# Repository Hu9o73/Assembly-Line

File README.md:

# Assembly Line

Projet Assembly Line : L'objectif étant de créer une machine fabricant des drones à la chaine.

Note: Par manque de fonds, le projet a été arrêté à la fin de la phase de conception. Le document UROP-PrésentationProjetComplet.pdf recense nos travaux.

Projet réalisé en collaboartion avec Théo Lissarague. Son profil GitHub peut être retrouvé dans la liste des contributeurs au projet.

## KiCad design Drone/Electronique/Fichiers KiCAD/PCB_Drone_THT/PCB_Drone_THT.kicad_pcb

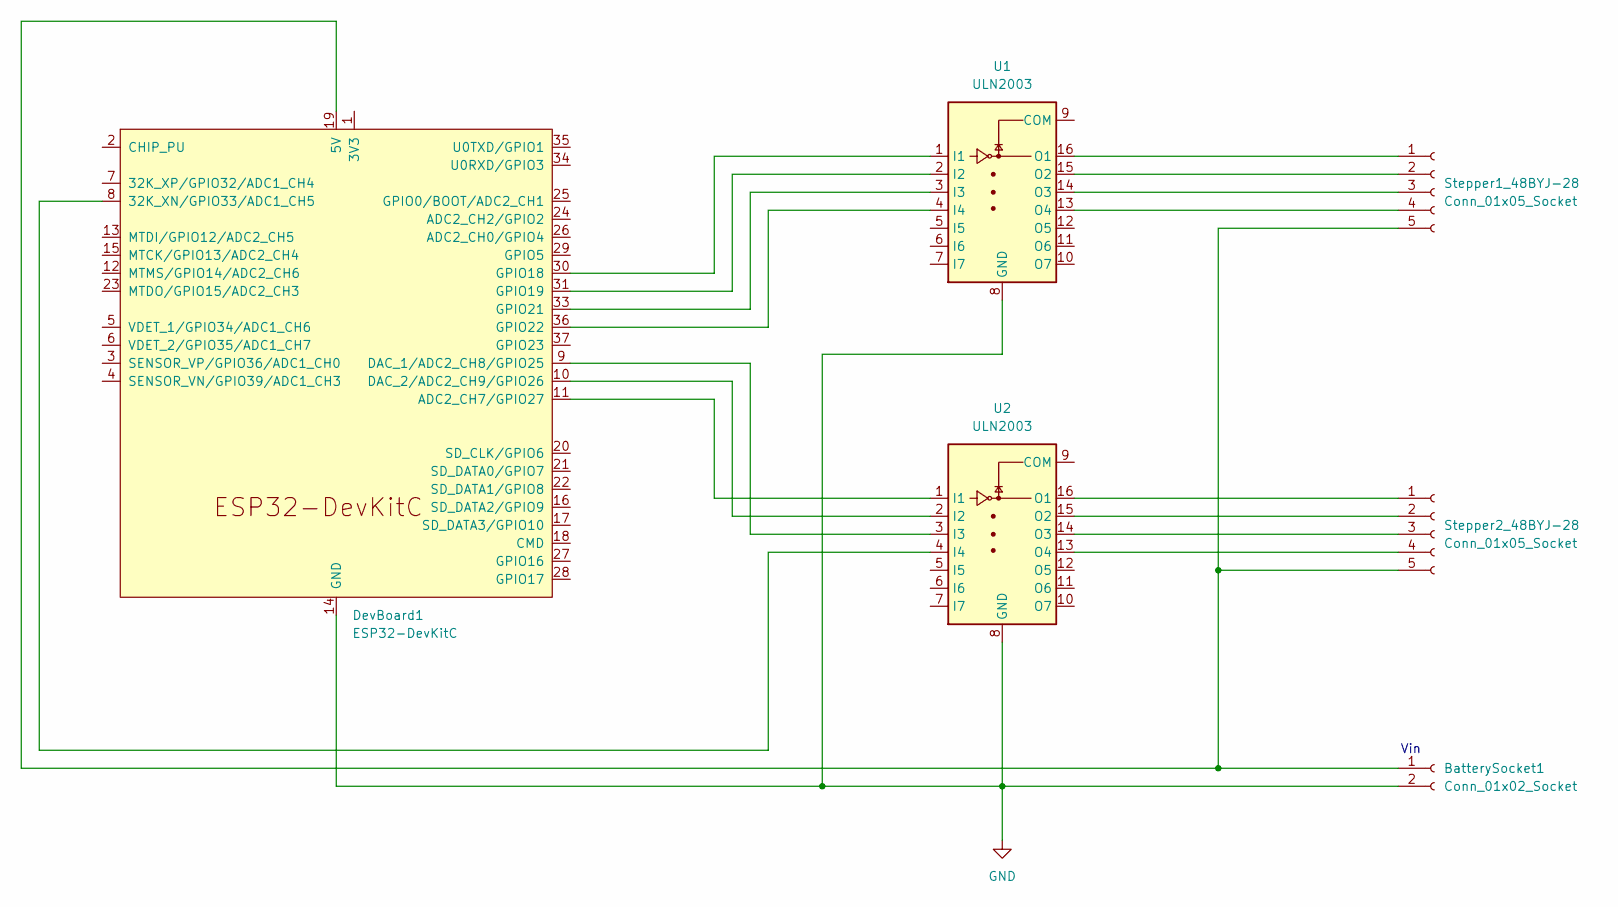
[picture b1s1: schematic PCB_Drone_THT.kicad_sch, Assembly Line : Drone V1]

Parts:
BatterySocket1: Conn_01x02_Socket; JST_XH_S2B-XH-A_1x02_P2.50mm_Horizontal
DevBoard1: ESP32-DevKitC
Stepper1_48BYJ-28, Stepper2_48BYJ-28: Conn_01x05_Socket; JST_XH_B5B-XH-A_1x05_P2.50mm_Vertical
U1, U2: ULN2003; DIP-16_W7.62mm_Socket_LongPads

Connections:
GND: BatterySocket1.2, DevBoard1.14 (GND), DevBoard1.32 (GND), DevBoard1.38 (GND), U1.8 (GND), U2.8 (GND)
unnamed: BatterySocket1.1, DevBoard1.19 (5V), Stepper1_48BYJ-28.5, Stepper2_48BYJ-28.5
unnamed: DevBoard1.8 (32K_XN/GPIO33/ADC1_CH5), U2.4 (I4)
unnamed: DevBoard1.11 (ADC2_CH7/GPIO27), U2.1 (I1)
unnamed: DevBoard1.9 (DAC_1/ADC2_CH8/GPIO25), U2.3 (I3)
unnamed: DevBoard1.10 (DAC_2/ADC2_CH9/GPIO26), U2.2 (I2)
unnamed: DevBoard1.30 (GPIO18), U1.1 (I1)
unnamed: DevBoard1.31 (GPIO19), U1.2 (I2)
unnamed: DevBoard1.33 (GPIO21), U1.3 (I3)
unnamed: DevBoard1.36 (GPIO22), U1.4 (I4)
unnamed: Stepper1_48BYJ-28.1, U1.16 (O1)
unnamed: Stepper1_48BYJ-28.2, U1.15 (O2)
unnamed: Stepper1_48BYJ-28.3, U1.14 (O3)
unnamed: Stepper1_48BYJ-28.4, U1.13 (O4)
unnamed: Stepper2_48BYJ-28.1, U2.16 (O1)
unnamed: Stepper2_48BYJ-28.2, U2.15 (O2)
unnamed: Stepper2_48BYJ-28.3, U2.14 (O3)
unnamed: Stepper2_48BYJ-28.4, U2.13 (O4)

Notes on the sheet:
Vin

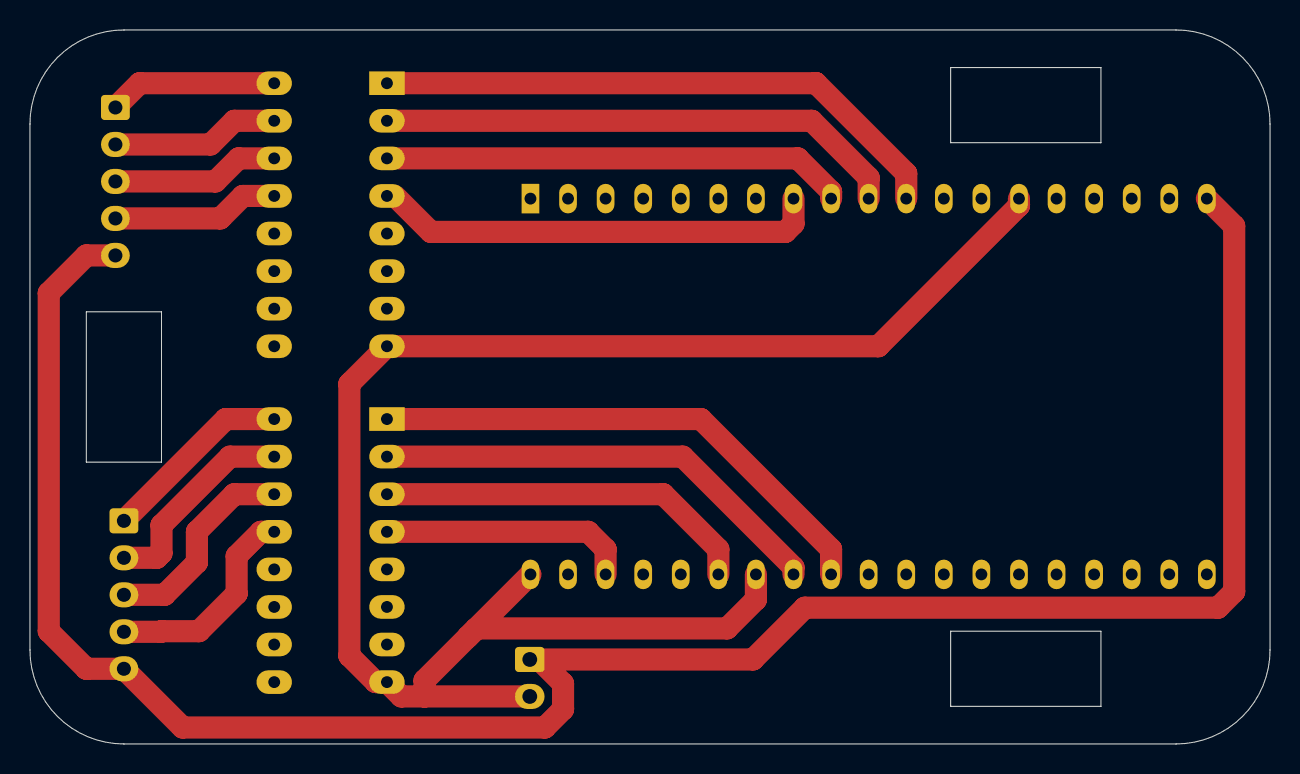
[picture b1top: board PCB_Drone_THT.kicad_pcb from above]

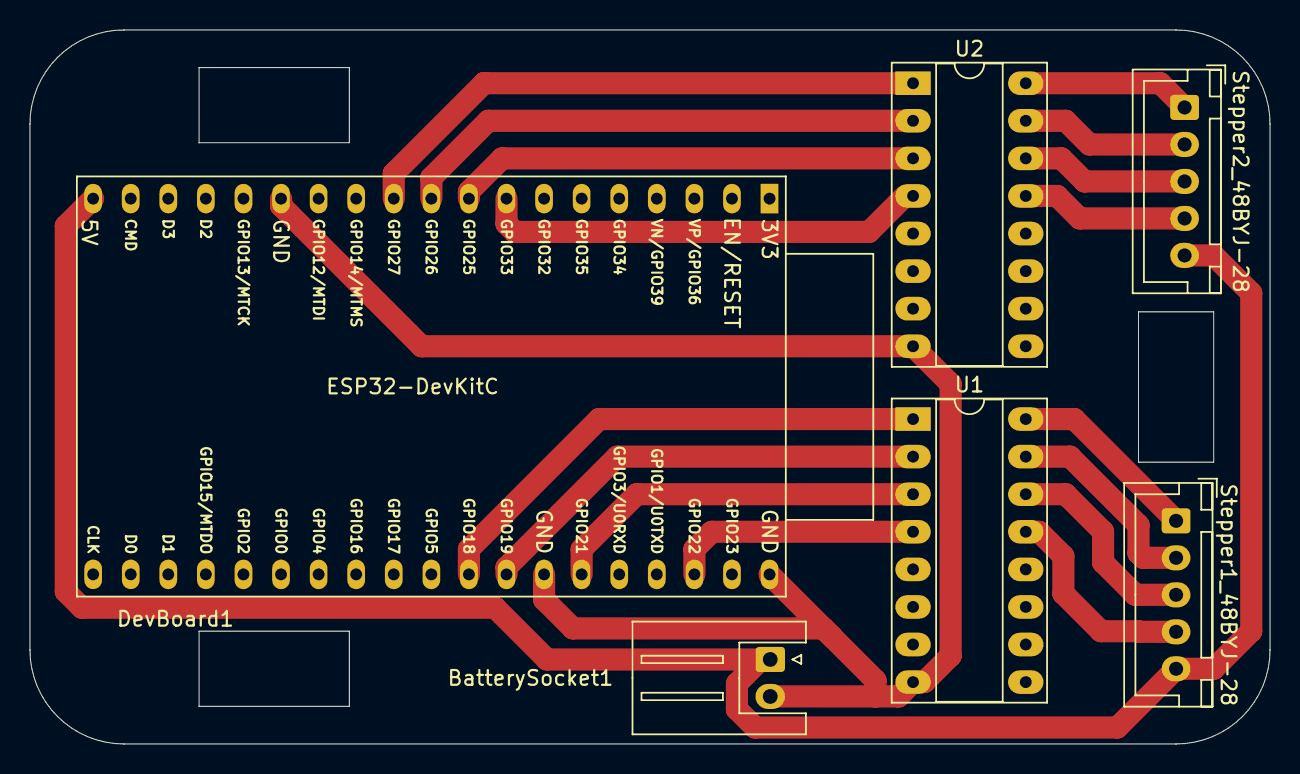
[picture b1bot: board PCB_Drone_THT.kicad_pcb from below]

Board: 2 copper layers, 83.8 x 48.3 mm, 6 parts (6 on the bottom side), 18 nets.

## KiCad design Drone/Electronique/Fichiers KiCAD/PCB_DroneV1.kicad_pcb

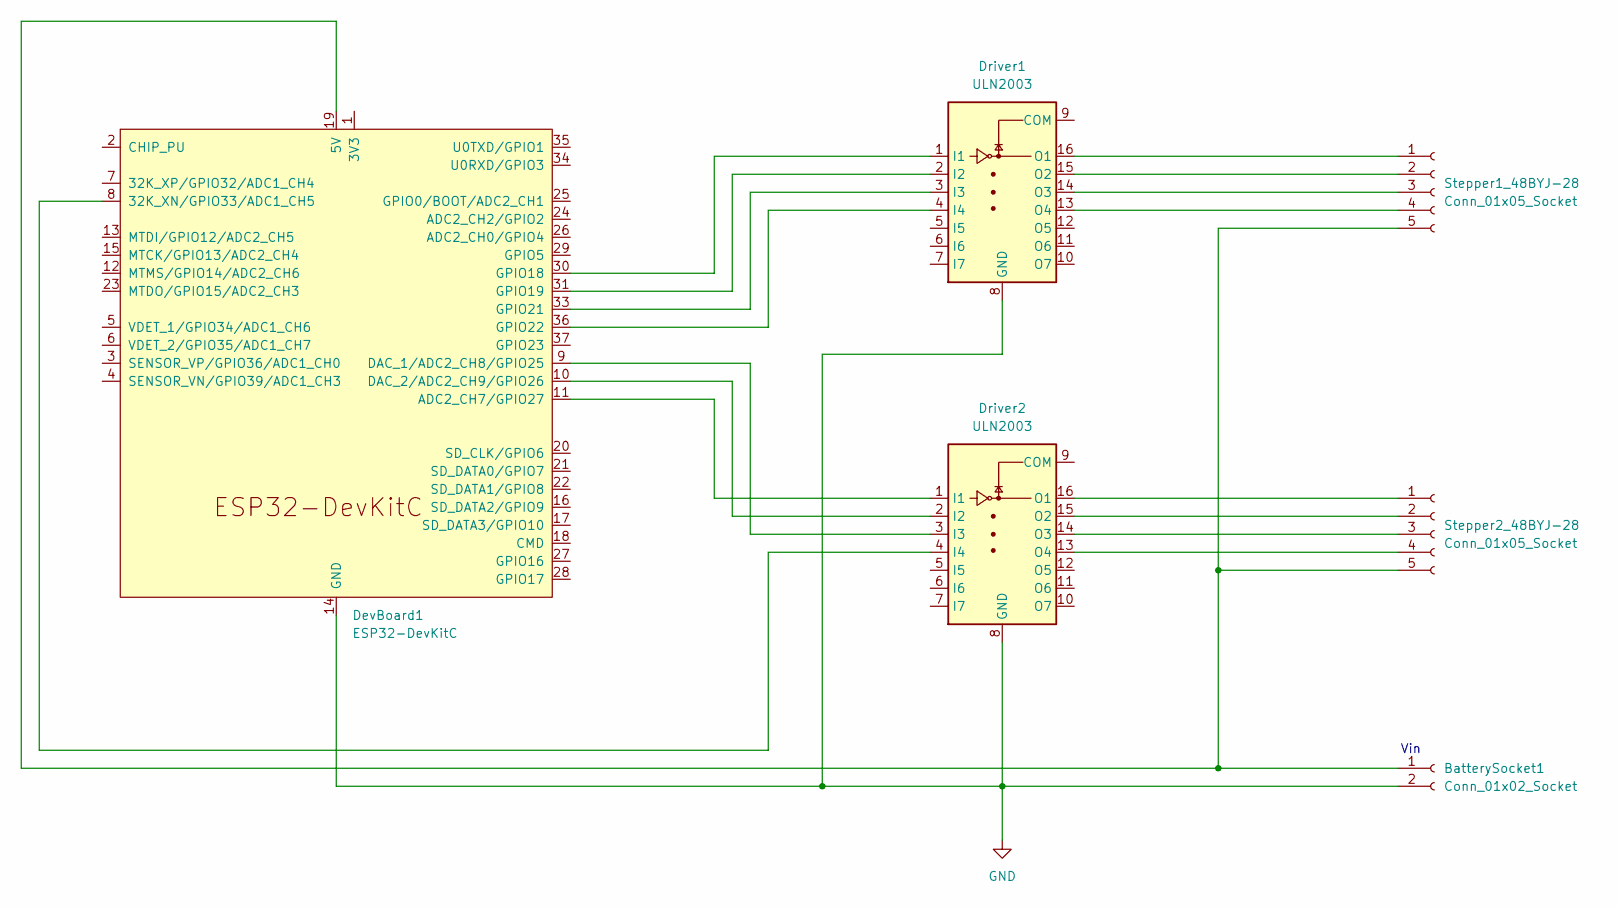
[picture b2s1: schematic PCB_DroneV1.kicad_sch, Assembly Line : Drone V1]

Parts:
BatterySocket1: Conn_01x02_Socket; JST_XH_S2B-XH-A_1x02_P2.50mm_Horizontal
DevBoard1: ESP32-DevKitC
Driver1, Driver2: ULN2003; DIP-16_W7.62mm_SMDSocket_SmallPads
Stepper1_48BYJ-28, Stepper2_48BYJ-28: Conn_01x05_Socket; JST_XH_B5B-XH-A_1x05_P2.50mm_Vertical

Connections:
GND: BatterySocket1.2, DevBoard1.14 (GND), DevBoard1.32 (GND), DevBoard1.38 (GND), Driver1.8 (GND), Driver2.8 (GND)
unnamed: BatterySocket1.1, DevBoard1.19 (5V), Stepper1_48BYJ-28.5, Stepper2_48BYJ-28.5
unnamed: DevBoard1.8 (32K_XN/GPIO33/ADC1_CH5), Driver2.4 (I4)
unnamed: DevBoard1.11 (ADC2_CH7/GPIO27), Driver2.1 (I1)
unnamed: DevBoard1.9 (DAC_1/ADC2_CH8/GPIO25), Driver2.3 (I3)
unnamed: DevBoard1.10 (DAC_2/ADC2_CH9/GPIO26), Driver2.2 (I2)
unnamed: DevBoard1.30 (GPIO18), Driver1.1 (I1)
unnamed: DevBoard1.31 (GPIO19), Driver1.2 (I2)
unnamed: DevBoard1.33 (GPIO21), Driver1.3 (I3)
unnamed: DevBoard1.36 (GPIO22), Driver1.4 (I4)
unnamed: Driver1.16 (O1), Stepper1_48BYJ-28.1
unnamed: Driver1.15 (O2), Stepper1_48BYJ-28.2
unnamed: Driver1.14 (O3), Stepper1_48BYJ-28.3
unnamed: Driver1.13 (O4), Stepper1_48BYJ-28.4
unnamed: Driver2.16 (O1), Stepper2_48BYJ-28.1
unnamed: Driver2.15 (O2), Stepper2_48BYJ-28.2
unnamed: Driver2.14 (O3), Stepper2_48BYJ-28.3
unnamed: Driver2.13 (O4), Stepper2_48BYJ-28.4

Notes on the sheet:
Vin

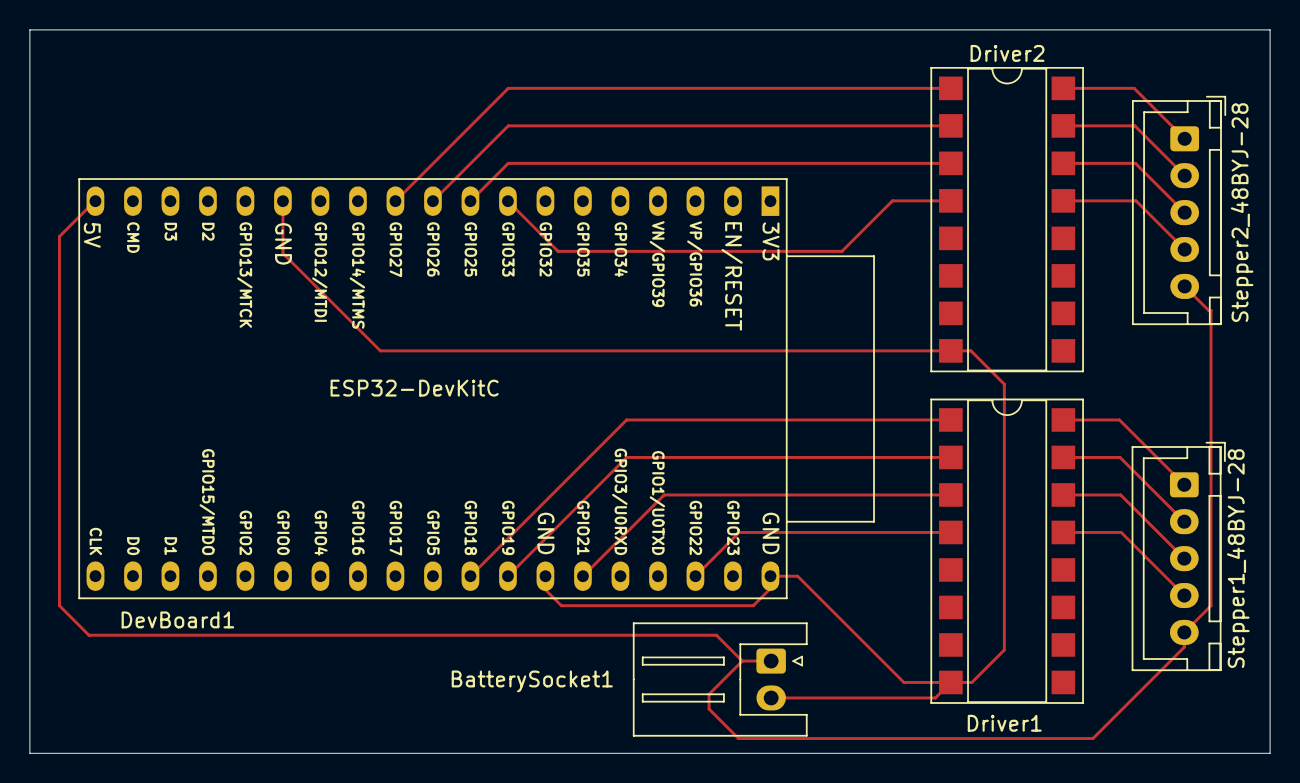
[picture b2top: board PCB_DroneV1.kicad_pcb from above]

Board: 2 copper layers, 84.0 x 49.0 mm, 6 parts (0 on the bottom side), 18 nets.

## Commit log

2024-03-06 Création dossier
2024-03-06 Déplacement fichier
2024-03-06 Suppression fichier inutile
2024-03-06 Rename Drone/Electronique/28byj48-Stepper-Motor-Datasheet.pdf to Drone/Electronique/Datasheet/28byj48-Stepper-Motor-Datasheet.pdf
2024-03-06 Rename Drone/Electronique/ULN2003-Datasheet.pdf to Drone/Electronique/Datasheet/ULN2003-Datasheet.pdf
2024-03-19 Add fichiers Kicad version THT et SMD
2024-04-19 Moteurs - Mécanique et Electronique
2024-10-09 Adding project pres pdf
